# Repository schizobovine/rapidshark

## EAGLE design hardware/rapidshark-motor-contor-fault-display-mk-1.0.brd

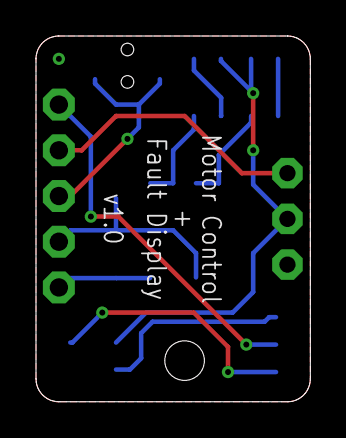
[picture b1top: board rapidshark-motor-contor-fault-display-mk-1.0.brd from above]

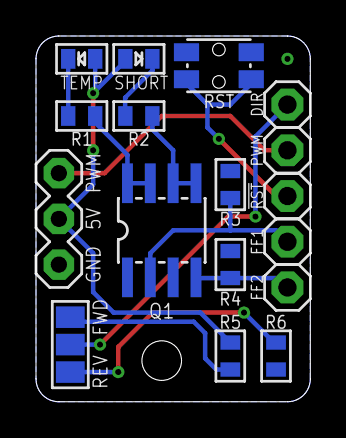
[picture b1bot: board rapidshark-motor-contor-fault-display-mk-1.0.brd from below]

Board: 2 copper layers, 15.2 x 20.3 mm, 18 parts (17 on the bottom side), 13 nets.

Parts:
!RST: M01PTH; 1X01
DIR: M01PTH; 1X01
FF1, FF2: M01PTH; 1X01
FRAME1: FRAME-LETTERNO_PACKAGE; DUMMY
FWD/BACK: PAD-JUMPER-3-NO_YES_SILK_FULL_BOX
JP1: M03PTH-CENTERED; 1X03-CENTERED
PWM: M01PTH; 1X01
Q1: MOSFET-NCHANNEL-DUALSOIC8; SO08
R1, R2: 470R; R0603-TIGHTER
R3, R4, R5, R6: 10K; R0603-TIGHTER
RST: SPST-NO-TACTCK-PTS840-GK; TACTILE-SMD-CK-PTS840-GK
SHORT: LED0603-TIGHT; LED-0603-TIGHT
TEMP: LED0603-TIGHT; LED-0603-TIGHT

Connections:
DIR: DIR.1, FWD/BACK.2
FF1: FF1.1, Q1.2, R3.1
FF2: FF2.1, Q1.4, R4.1
GND: JP1.1, Q1.1, Q1.3, R3.2, R4.2, R6.2, RST.3, RST.4
unnamed: R1.2, TEMP.C
unnamed: Q1.7, Q1.8, R1.1
unnamed: R2.2, SHORT.C
unnamed: Q1.5, Q1.6, R2.1
unnamed: FWD/BACK.1, R5.2
unnamed: FWD/BACK.3, R6.1
PWM: JP1.3, PWM.1
RST: !RST.1, RST.1, RST.2
VCC: JP1.2, R5.1, SHORT.A, TEMP.A

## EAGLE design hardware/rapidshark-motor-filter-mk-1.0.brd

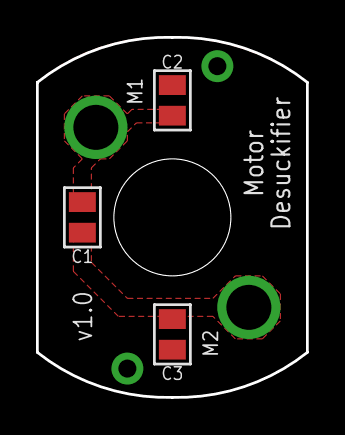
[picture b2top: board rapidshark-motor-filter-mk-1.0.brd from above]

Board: 2 copper layers, 15.0 x 20.0 mm, 8 parts (1 on the bottom side), 3 nets, no tracks yet.

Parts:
C1, C2, C3: 1uF; C0805-TIGHTER
FRAME1: FRAME-LETTERNO_PACKAGE; DUMMY
M1, M2: M01PTH-2.5MM; 1X01-2.5MM
M1-CHASSIS, M2-CHASSIS: M01SMDNS; 1X01NS

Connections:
CHASSIS: C2.1, C3.1, M1-CHASSIS.1, M2-CHASSIS.1
M1: C1.2, C2.2, M1.1
M2: C1.1, C3.2, M2.1

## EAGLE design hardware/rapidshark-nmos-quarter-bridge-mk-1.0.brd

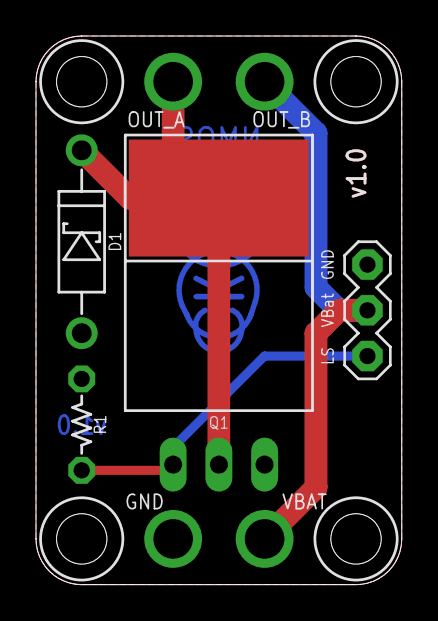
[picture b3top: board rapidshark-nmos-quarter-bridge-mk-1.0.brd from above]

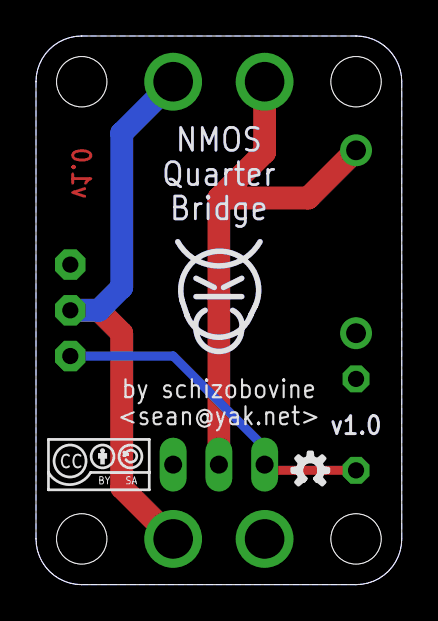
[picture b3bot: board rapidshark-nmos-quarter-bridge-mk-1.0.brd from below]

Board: 2 copper layers, 20.3 x 30.5 mm, 12 parts (4 on the bottom side), 4 nets.

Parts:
D1: 1N5819; DIODE-SCHOTTKY-10.16MM
FRAME1: FRAME-LETTERNO_PACKAGE; DUMMY
GND: M0112AWG; 1X01-12AWG
JP1: M03PTH-CENTERED; 1X03-CENTERED
OUT_A: M0112AWG; 1X01-12AWG
OUT_B: M0112AWG; 1X01-12AWG
Q1: STP60NF06L; TO220-THERMPAD
R1: 10k; RESISTOR-AXIAL-PTH-5.08MM
U$1: COW_SMALL_METAL_NOTEXT
U$2: CC-BY-SA-4.0-NO-URL
U$3: OSHWLOGO_TINY_SILKONLY
VBAT: M0112AWG; 1X01-12AWG

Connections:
A: D1.C, OUT_A.1, Q1.2@1, Q1.2@2
GND: D1.A, GND.1, JP1.1, Q1.3, R1.P$1
LS: JP1.3, Q1.1, R1.P$2
V_BATT: JP1.2, OUT_B.1, VBAT.1

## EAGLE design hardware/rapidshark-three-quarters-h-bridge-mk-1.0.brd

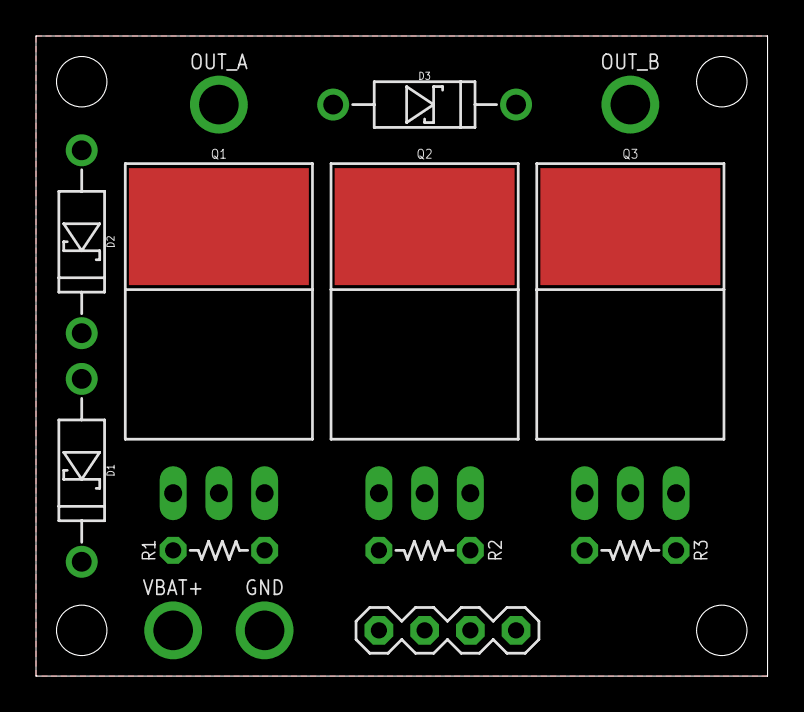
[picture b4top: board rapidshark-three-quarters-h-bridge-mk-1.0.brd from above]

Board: 2 copper layers, 40.6 x 35.6 mm, 15 parts (1 on the bottom side), 7 nets, no tracks yet.

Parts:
D1, D2, D3: 1N5819; DIODE-SCHOTTKY-10.16MM
FRAME1: FRAME-LETTERNO_PACKAGE; DUMMY
GND: M0112AWG; 1X01-12AWG
JP1: M04PTH; 1X04-PTH-VERT
OUT_A: M0112AWG; 1X01-12AWG
OUT_B: M0112AWG; 1X01-12AWG
Q1: FQP30N06L; TO220-THERMPAD
Q2, Q3: STP60NF06L; TO220-THERMPAD
R1, R2, R3: 10k; RESISTOR-AXIAL-PTH-5.08MM
VBAT+: M0112AWG; 1X01-12AWG

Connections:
A: D1.A, D2.C, OUT_A.1, Q1.2@1, Q1.2@2, Q2.2@1, Q2.2@2
GND: D2.A, D3.A, GND.1, JP1.1, Q2.3, Q3.3, R2.P$1, R3.P$1
HS: Q1.1, R1.P$1
LS_A: Q2.1, R2.P$2
LS_B: Q3.1, R3.P$2
unnamed: D3.C, OUT_B.1, Q3.2@1, Q3.2@2
V_BATT: D1.C, Q1.3, R1.P$2, VBAT+.1

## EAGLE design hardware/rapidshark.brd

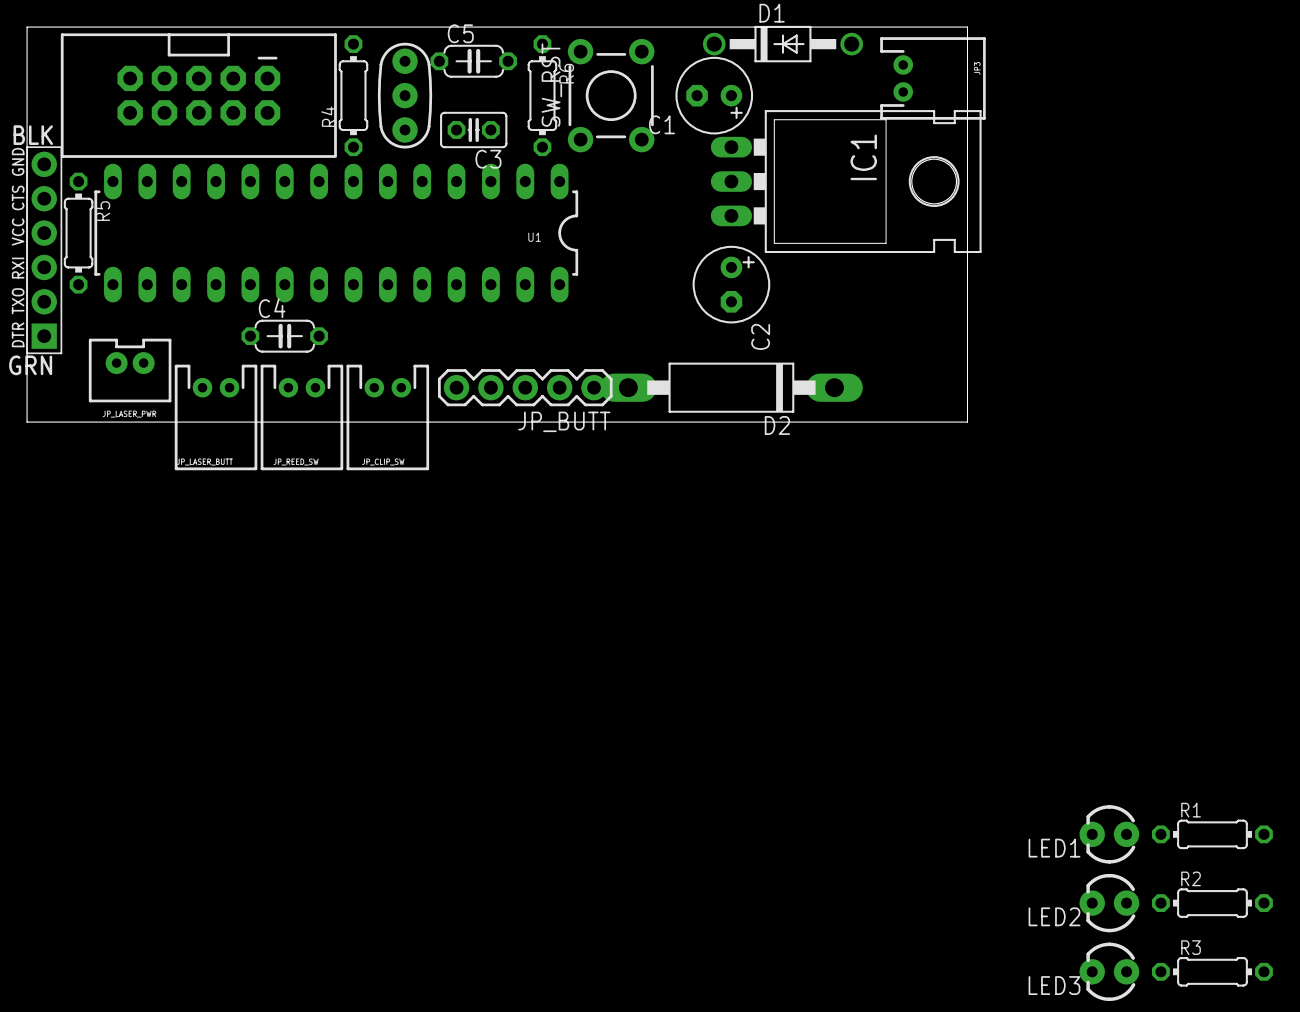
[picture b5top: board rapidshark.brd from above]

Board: 2 copper layers, 69.5 x 29.2 mm, 28 parts (0 on the bottom side), 31 nets, no tracks yet.

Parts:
C1, C2: 100uF; E2,5-6
C3: 1uF; C025-025X050
C4: 1uF; C050-024X044
C5: 0.1uF; C050-024X044
D1: 1N4004; DO41-10
D2: P6KEXXC; CB417-15
IC1: L7805; TO-220-ALT
ISP: FTDI_DEVICE; FTDI_DEVICE_SIDE
JP3: M02JST-PTH-2; JST-2-PTH
JP_BUTT: 1X05
JP_CLIP_SW: M02JST-PTH-2; JST-2-PTH
JP_DISPLAY: M05X2SHD; 2X5-SHROUDED
JP_LASER_BUTT: M02JST-PTH-2; JST-2-PTH
JP_LASER_PWR: M02JST-PTH-VERT; JST-2-PTH-VERT
JP_REED_SW: M02JST-PTH-2; JST-2-PTH
LED1: RED; LED3MM
LED2: GREEN; LED3MM
LED3: YELLOW; LED3MM
R1, R2, R3, R4, R5: 220R; 0204/7
R6: 10K; 0204/7
SW_RST: SWITCH-MOMENTARY-2PTH; TACTILE-PTH
U1: ATMEGA328P_PDIP; DIL28-3
Y1: RESONATOR-PTH

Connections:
DIG_1: R4.1, U1.16
DIG_2: R5.2, U1.17
GND: C1.-, C2.-, C3.2, C4.2, D2.C, IC1.GND, ISP.P$5, ISP.P$6, JP3.2, JP_BUTT.1, JP_CLIP_SW.2, JP_LASER_PWR.2, JP_REED_SW.2, LED1.K, LED2.K, SW_RST.3, U1.8, U1.22, Y1.2
unnamed: U1.9, Y1.3
unnamed: C5.2, R6.1, SW_RST.1, U1.1
unnamed: U1.10, Y1.1
unnamed: LED2.A, R2.1
unnamed: C5.1, ISP.P$1
unnamed: ISP.P$2, U1.3
unnamed: ISP.P$3, U1.2
unnamed: JP_DISPLAY.5, R4.2
unnamed: JP_DISPLAY.10, R5.1
unnamed: JP_LASER_BUTT.1, JP_LASER_PWR.1, R1.2
unnamed: JP_BUTT.5, U1.23
unnamed: JP_BUTT.4, U1.24
unnamed: JP_BUTT.3, U1.25
unnamed: JP_BUTT.2, U1.26
unnamed: LED1.A, R1.1
unnamed: JP_CLIP_SW.1, U1.27
unnamed: JP_REED_SW.1, U1.28
unnamed: LED3.A, R3.1
unnamed: LED3.K, U1.4
SEG_A: JP_DISPLAY.7, U1.5
SEG_B: JP_DISPLAY.6, U1.6
SEG_C: JP_DISPLAY.4, U1.11
SEG_D: JP_DISPLAY.1, U1.12
SEG_E: JP_DISPLAY.3, U1.13
SEG_F: JP_DISPLAY.8, U1.14
SEG_G: JP_DISPLAY.9, U1.15
VCC: C2.+, C3.1, C4.1, D1.A, IC1.OUT, ISP.P$4, JP_LASER_BUTT.2, R2.2, R3.2, R6.2, U1.7, U1.20, U1.21
VIN: C1.+, D1.C, D2.A, IC1.IN, JP3.1

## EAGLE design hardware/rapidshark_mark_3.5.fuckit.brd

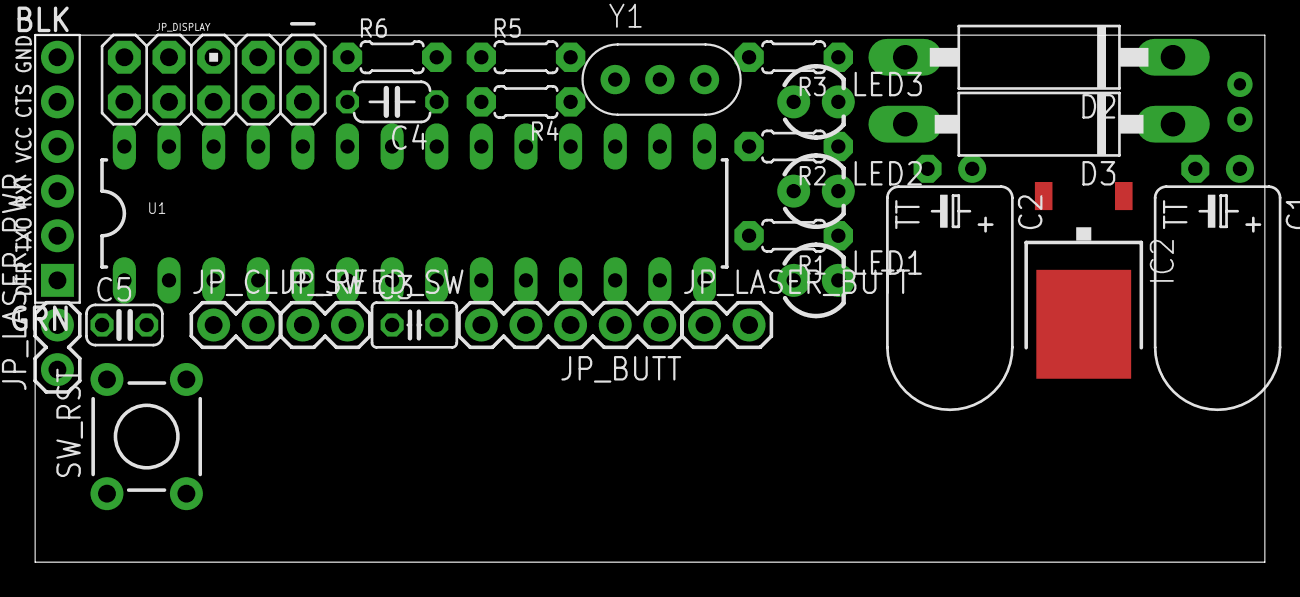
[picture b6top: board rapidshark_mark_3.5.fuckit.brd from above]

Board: 2 copper layers, 70.0 x 30.0 mm, 28 parts (1 on the bottom side), 32 nets, no tracks yet.

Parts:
C1, C2: 100uF; TT2D7L
C3: 1uF; C025-025X050
C4: 1uF; C050-024X044
C5: 0.1uF; C025-024X044
D2: P6KEXXC; CB417-15
D3: P6KEXXA; C1702-15
IC2: 7805DT; TO252
ISP: FTDI_DEVICE; FTDI_DEVICE_SIDE
JP3: M02JST-PTH-2; JST-2-PTH
JP_BUTT: BUTTS; 1X05
JP_CLIP_SW: M02PTH; 1X02
JP_DISPLAY: M05X2PTH; AVR_ICSP
JP_LASER_BUTT: M02PTH; 1X02
JP_LASER_PWR: M02PTH; 1X02
JP_REED_SW: M02PTH; 1X02
LED1: RED; LED3MM
LED2: GREEN; LED3MM
LED3: YELLOW; LED3MM
R1, R2, R3, R4, R5: 220R; 0204/5
R6: 10K; 0204/5
SW_RST: SWITCH-MOMENTARY-2PTH; TACTILE-PTH
U1: ATMEGA328P_PDIP; DIL28-3
Y1: 16MLOLZ; CERM_OSC

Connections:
DIG_1: R4.1, U1.17
DIG_2: R5.2, U1.27
GND: C1.-, C2.-, C3.2, C4.2, D2.C, D3.A, IC2.3, ISP.P$5, ISP.P$6, JP3.2, JP_BUTT.5, JP_CLIP_SW.2, JP_LASER_PWR.2, JP_REED_SW.2, LED1.K, LED2.K, SW_RST.3, U1.8, U1.22, Y1.P$2
unnamed: U1.10, Y1.P$3
unnamed: C5.2, R6.1, SW_RST.1, U1.1
unnamed: U1.9, Y1.P$1
unnamed: LED2.A, R2.1
unnamed: C5.1, ISP.P$1
unnamed: ISP.P$2, U1.3
unnamed: ISP.P$3, U1.2
unnamed: JP_BUTT.4, U1.11
unnamed: JP_DISPLAY.5, R4.2
unnamed: JP_BUTT.3, U1.12
unnamed: JP_BUTT.2, U1.13
unnamed: JP_BUTT.1, U1.14
unnamed: JP_DISPLAY.10, R5.1
unnamed: JP_CLIP_SW.1, U1.4
unnamed: JP_REED_SW.1, U1.5
unnamed: LED3.K, U1.15
unnamed: JP_LASER_BUTT.1, JP_LASER_PWR.1, R1.2
unnamed: LED1.A, R1.1
unnamed: LED3.A, R3.1
SEG_A: JP_DISPLAY.7, U1.6
SEG_B: JP_DISPLAY.6, U1.25
SEG_C: JP_DISPLAY.4, U1.24
SEG_D: JP_DISPLAY.1, U1.16
SEG_DP: JP_DISPLAY.2, U1.18
SEG_E: JP_DISPLAY.3, U1.23
SEG_F: JP_DISPLAY.8, U1.26
SEG_G: JP_DISPLAY.9, U1.28
VCC: C2.+, C3.1, C4.1, D3.C, IC2.2, ISP.P$4, JP_LASER_BUTT.2, R2.2, R3.2, R6.2, U1.7, U1.20, U1.21
VIN: C1.+, D2.A, IC2.1, JP3.1

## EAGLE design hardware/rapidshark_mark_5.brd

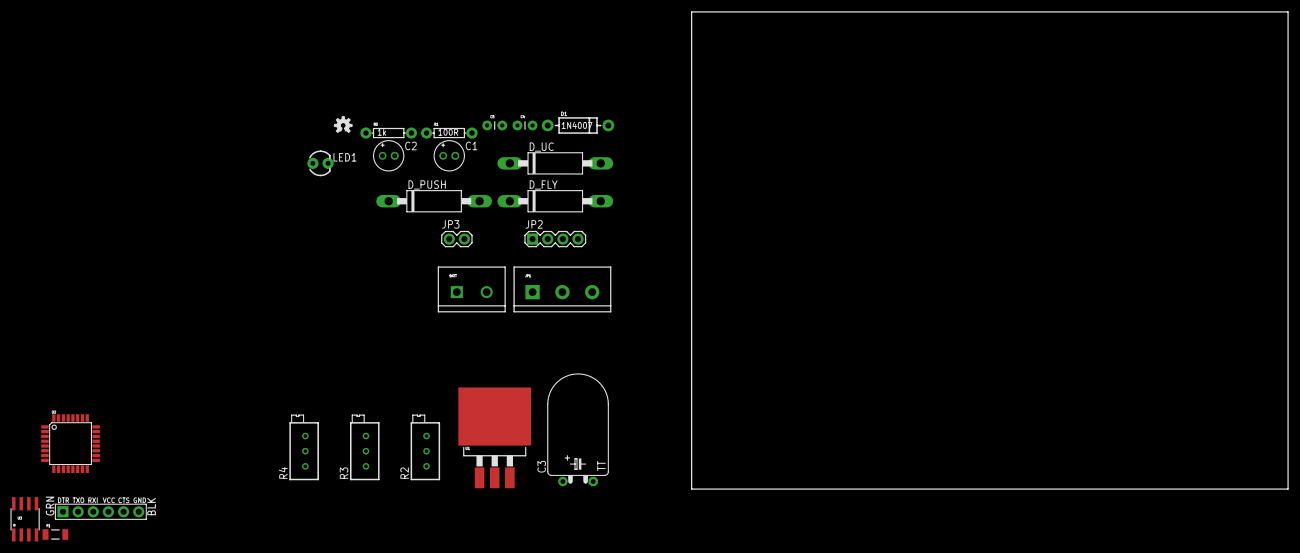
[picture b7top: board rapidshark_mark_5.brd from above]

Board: 2 copper layers, 100.0 x 80.0 mm, 26 parts (0 on the bottom side), 7 nets, no tracks yet.

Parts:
BATT: LIPO4S_14.8V_EXT5MMSCREW; 1X02_5MM_SCREW
C1, C2: 10uF; E2-5
C3: 150uF; TT5D11L
C4, C5: 1uF; CAP-PTH-SMALL
D1: 1N4007; DIODE-1N4001
D_FLY: P6KEXXC; CB417-15
D_PUSH: P6KEXXC; CB417-15
D_UC: P6KEXXC; CB417-15
F1: PTCSMD-W; PTC-1206-WIDE
FRAME1: FRAME-LETTER; CREATIVE_COMMONS
JP1: TRG_ASM_CON; SCREWTERMINAL-5MM-3
JP2: SPEED_SELECT; 1X04
JP3: UC_PWR_CON; 1X02
JP4: FTDI_DEVICE; FTDI_DEVICE_SIDE
LED1: GREEN; LED3MM
LOGO1: OSHW-LOGOS; OSHW-LOGO-S
R1: 100R; AXIAL-0.3
R2, R4: 1k; RTRIMT93XA
R3: 2k; RTRIMT93XA
R5: 1k; AXIAL-0.3
U1: V_REG_LD1085D2; D2PACK/A
U2: ATMEGA328P; TQFP32-08
U3: MC34063SMD; SO08

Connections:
ADJ: C2.+, C4.1, D1.A, R1.P$1, R2.2, R3.2, R4.2, U1.1
GND: BATT.1, C1.-, C2.-, C3.-, C4.2, C5.2, D_FLY.C, D_PUSH.C, JP1.3, JP2.4, JP3.2, LED1.K, R2.1
unnamed: JP2.2, R3.1
unnamed: JP2.1, R4.1
unnamed: LED1.A, R5.P$1
V_BATT: C1.+, JP1.1, JP3.1, U1.3
V_OUT: C3.+, C5.1, D1.C, JP1.2, R1.P$2, R5.P$2, U1.2, U1.TAB

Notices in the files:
parts and their libraries:
SparkFun-PowerIC: Licensing: Creative Commons ShareAlike 4.0 International - https://creativecommons.org/licenses/by-sa/4.0
SparkFun-Aesthetics: Released under the Creative Commons Attribution Share-Alike 4.0 License
SparkFun-Aesthetics: https://creativecommons.org/licenses/by-sa/4.0
